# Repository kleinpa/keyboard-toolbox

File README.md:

# keyboard-toolkit

This repository contains tools for designing computer keyboards using
code. It brings together [KiCad](https://gitlab.com/kicad/code/kicad),
[exdxf](https://ezdxf.mozman.at/),
[Shapely](https://github.com/Toblerity/Shapely), and
[Bazel](https://bazel.build/) to hopefully make building keyboards a
little bit more like building a web site. Designing hardware with code
ideally enables fast iteration on key positions other design choices
with the support of an automated build system. It also means that a
single source of truth can be used to generate both the electrical
schematic and firmware.

## Overview

To build a keyboard with this library, just write a [small python
program](examples/build_numpad17.py) that generates a list of key
positions (and a few other things) and records that information in a
Keyboard protobuf message. Tools in this repository can use the
Keyboard message to generate PCBs, plates, firmware, and more. Some
post-processing, like PCB routing, will need to be done by hand but
hopefully it's less work than the alternatives.

Once a program exists to generate the keyboard definition, the Bazel
build system can be used to feed it's output into the generator tools
provided by this reposiory.

## Features

### Output Generation

- Generate Switch plates in DXF, SVG formats
- Generate unrouted PCBs with all required components
- [QMK info.json files](https://beta.docs.qmk.fm/developing-qmk/qmk-reference/reference_info_json)
- Generate [KLE JSON](http://www.keyboard-layout-editor.com/) data
- (Untested) Generate FR4 switch plates

### Input and Processing

- Load [KLE JSON](http://www.keyboard-layout-editor.com/) data
- Generate form-fitting PCBs and Plates based on the key arrangment
- Configure switch matrix positions based on the key arrangment

### Microcontrollers

- ATmega32u4
- Pro Micro
- (Untested) STM32F072

### Switchs

For now this project is focused on switch-specific PCBs.

- [Cherry MX](https://deskthority.net/wiki/Cherry_MX) compatible
- (WIP) [Kailh PG1350](https://deskthority.net/wiki/Kailh_PG1350_series)
- (WIP) [ALPS](https://deskthority.net/wiki/Alps_SKCL/SKCM_series) compatible

### Cases

Keyboard case come in many differnet styles are some of the least
trivial parts to generate. To keep things simple this repository only
supports the "PCB-to-Base-Plate Sandwich". This is a minimalist
approach where the PCB is attached to a base plate with standoffs and
an optional switch plate is 'floating' on the switches. Additional
case types may be added eventually and would be a welcome addition to
this library.

## Getting Started

This project uses the Bazel build system internally and also provides
build rules for downstream projects. Additionally, PCB file
processing is provided by the
[`kicad-bazel`](https://github.com/kleinpa/kicad-bazel) project which
works by building KiCAD from source
([issue](https://github.com/kleinpa/kicad-bazel/issues/2)). All tools
that interact with PCBs unfortunately depend on all of KiCAD's build
dependencies.

## Bazel Build Rules

It makes sense to use some tool to generate the keyboard proto and
here is an example of stock Baezl rules can be used to make that
happen:

```python
py_binary(
    name = "build_kbxyz",
    srcs = ["build_kbxyz.py"],
    deps = [
        "//kbtb:keyboard_lib",
    ],
)

genrule(
    name = "kbxyz_proto",
    outs = ["kbxyz.pb"],
    cmd = "$(execpath :build_kbxyz) $@",
    exec_tools = [":build_kbxyz"],
)
```

### build_keyboard

This is the main entry point to the output generation tools provided by this repository.

```python
load("@keyboard_toolbox//kbtb:defs.bzl", "build_keyboard")

build_keyboard(
    name = "kbxyz",
    src = ":kbxyz_proto",
)
```

The following files can be requested from this rule:

- `kbxyz.svg`
- `kbxyz.kicad_pcb`
- `kbxyz-info.json`
- `kbxyz_plate_top.dxf`
- `kbxyz_plate_top.kicad_pcb`
- `kbxyz_plate_bottom.dxf`
- `kbxyz_plate_bottom.kicad_pcb`

### kbpb_from_kle

This is an experimenal build rule that can produce a basic keyboard
from a kle file is also provided. It's probably more flexible to just
do this via python like in the genrule example above.

```python
load("@keyboard_toolbox//kbtb:defs.bzl", "kbpb_from_kle")

kbpb_from_kle(
    name = "kbxyz_proto",
    src = "kbxyz-kle.json",
)
```

## The Future

The biggest question that remains unanswered is: _Why just keyboards?_
If there's one thing I've figured out while working on this project is
that the idea of generating electronic hardware with software is worth
exploring more.

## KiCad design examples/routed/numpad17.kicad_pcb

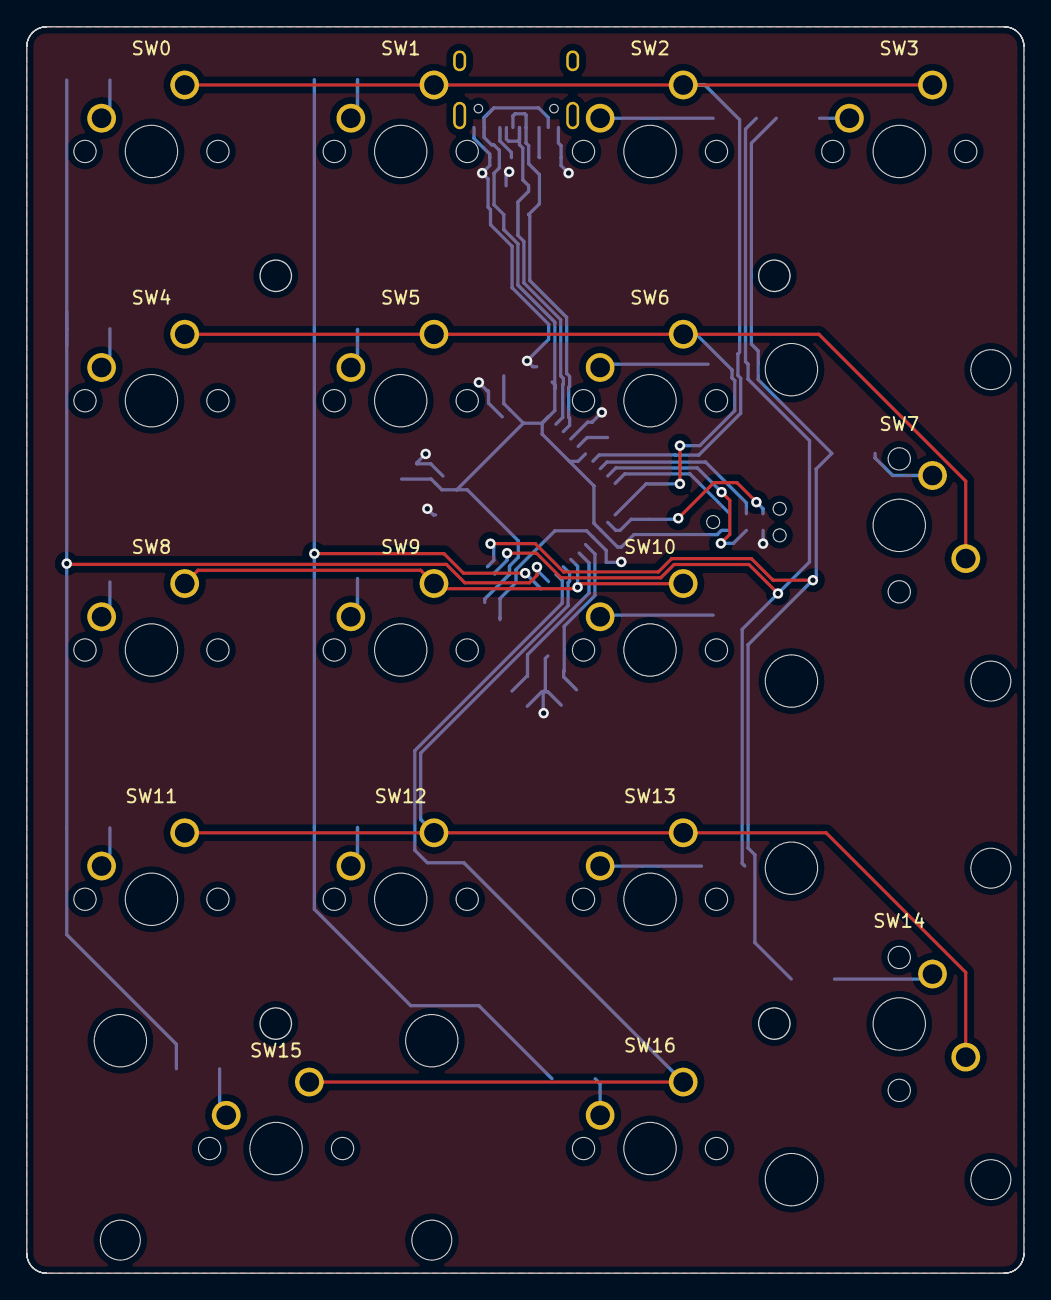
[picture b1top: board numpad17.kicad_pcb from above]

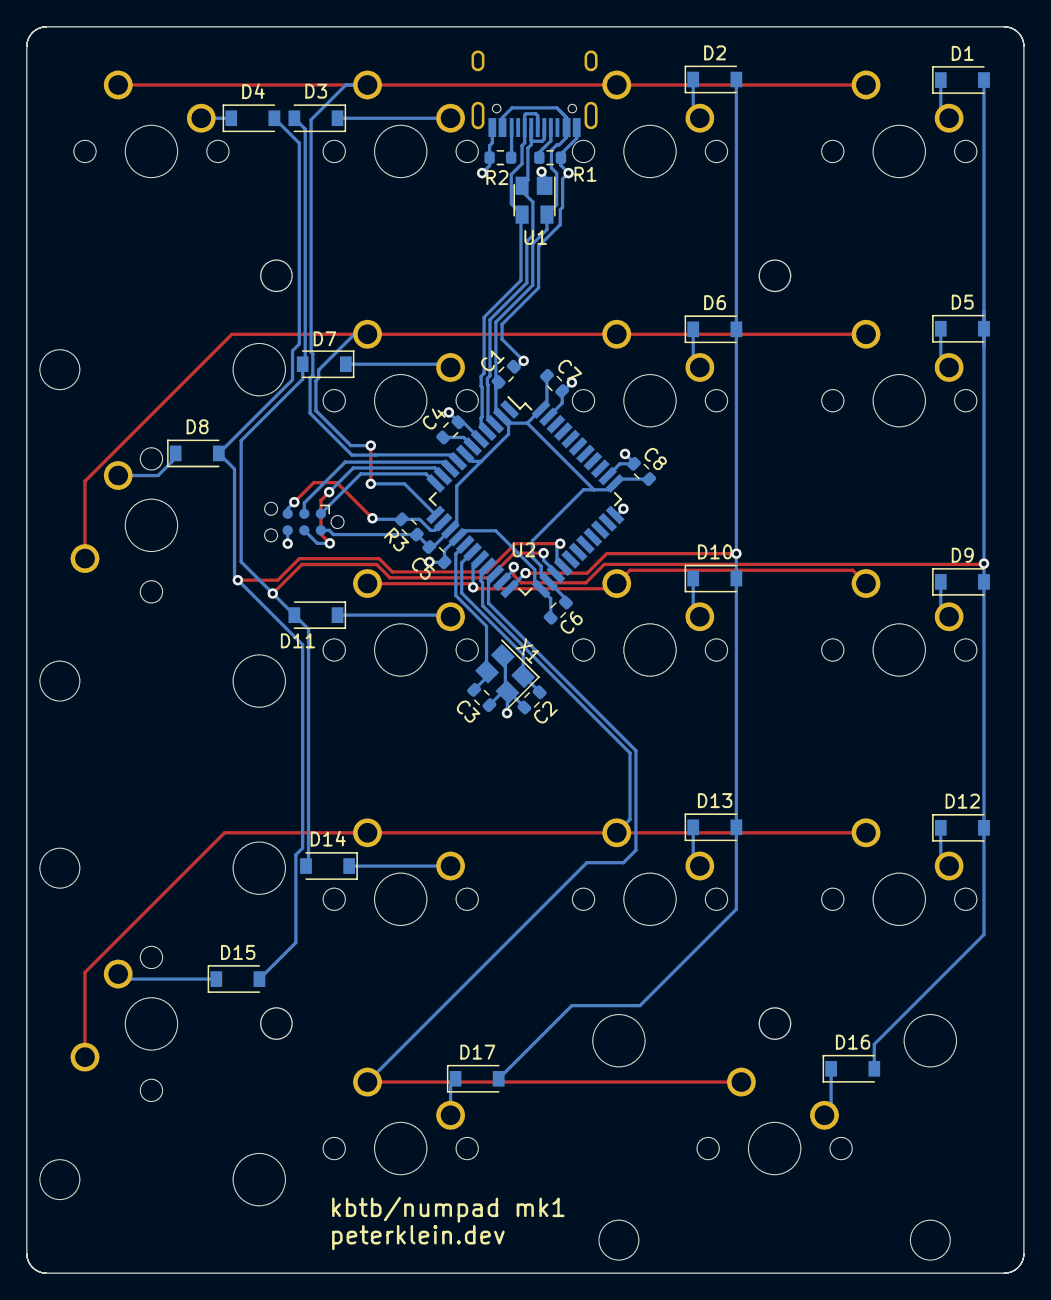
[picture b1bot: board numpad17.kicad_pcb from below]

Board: 2 copper layers, 76.2 x 95.2 mm, 53 parts (33 on the bottom side), 39 nets.

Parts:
C1: 10 µF; R_0603_1608Metric
C2, C3: 22 pF; R_0603_1608Metric
C4: 1 µF; R_0603_1608Metric
C5, C6, C7, C8: 0.1 µF; R_0603_1608Metric
D1, D2, D3, D4, D5, D6, D7, D8, D9, D10, D11, D12, D13, D14, D15, D16, D17: 4148; D_SOD-123
J1: HRO-TYPE-C-31-M-12
Jx1: Tag-Connect_TC2030-IDC-NL_2x03_P1.27mm_Vertical
R1, R2: 5.1 kΩ; R_0603_1608Metric
R3: 10 kΩ; R_0603_1608Metric
ST7, ST14, ST15: SW_Cherry_MX_2.00u_PCB; Stab_Cherry_MX_2.00u_PCB
SW0, SW1, SW2, SW3, SW4, SW5, SW6, SW7, SW8, SW9, SW10, SW11, SW12, SW13, SW14, SW15, SW16: SW_Cherry_MX_1.00u_PCB; SW_Cherry_MX_PCB
U1: SR05; SOT-143
U2: ATMEGA32U4-AU; TQFP-44_10x10mm_P0.8mm
X1: 16 MHz; Crystal_SMD_3225-4Pin_3.2x2.5mm

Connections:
GND: C1.1, C2.2, C3.2, C4.1, C5.1, C6.2, C7.1, C8.2, J1.1, J1.12, Jx1.6, R1.1, R2.2, U1.1, U2.5, U2.15, U2.23, U2.33, U2.35, U2.43, X1.2, X1.4
icsp-miso: Jx1.1, U2.11
icsp-mosi: Jx1.4, U2.10
icsp-reset: Jx1.5, R3.2, U2.13
icsp-sck: Jx1.3, U2.9
matrix-0: SW0.1, SW1.1, SW2.1, SW3.1, U2.8
matrix-1: SW4.1, SW5.1, SW6.1, SW7.1, U2.12
matrix-2: SW8.1, SW9.1, SW10.1, U2.18
matrix-3: SW11.1, SW12.1, SW13.1, SW14.1, U2.19
matrix-4: SW15.1, SW16.1, U2.20
matrix-5: D1.2, D5.2, D9.2, D12.2, D16.2, U2.21
matrix-6: D2.2, D6.2, D10.2, D13.2, D17.2, U2.22
matrix-7: D3.2, D7.2, D11.2, D14.2, U2.25
matrix-8: D4.2, D8.2, D15.2, U2.26
switch-diode-0: D1.1, SW0.2
switch-diode-1: D2.1, SW1.2
switch-diode-2: D3.1, SW2.2
switch-diode-3: D4.1, SW3.2
switch-diode-4: D5.1, SW4.2
switch-diode-5: D6.1, SW5.2
switch-diode-6: D7.1, SW6.2
switch-diode-7: D8.1, SW7.2
switch-diode-8: D9.1, SW8.2
switch-diode-9: D10.1, SW9.2
switch-diode-10: D11.1, SW10.2
switch-diode-11: D12.1, SW11.2
switch-diode-12: D13.1, SW12.2
switch-diode-13: D14.1, SW13.2
switch-diode-14: D15.1, SW14.2
switch-diode-15: D16.1, SW15.2
switch-diode-16: D17.1, SW16.2
ucap: C4.2, U2.6
usb-cc1: J1.4, R1.2
usb-cc2: J1.10, R2.1
usb-dn: J1.5, J1.7, U1.2, U2.3
usb-dp: J1.6, J1.8, U1.3, U2.4
usb-vcc: C1.2, C5.2, C6.1, C7.2, C8.1, J1.2, J1.11, Jx1.2, R3.1, U1.4, U2.2, U2.7, U2.14, U2.24, U2.34, U2.44
xtal1: C2.1, U2.17, X1.1
xtal2: C3.1, U2.16, X1.3

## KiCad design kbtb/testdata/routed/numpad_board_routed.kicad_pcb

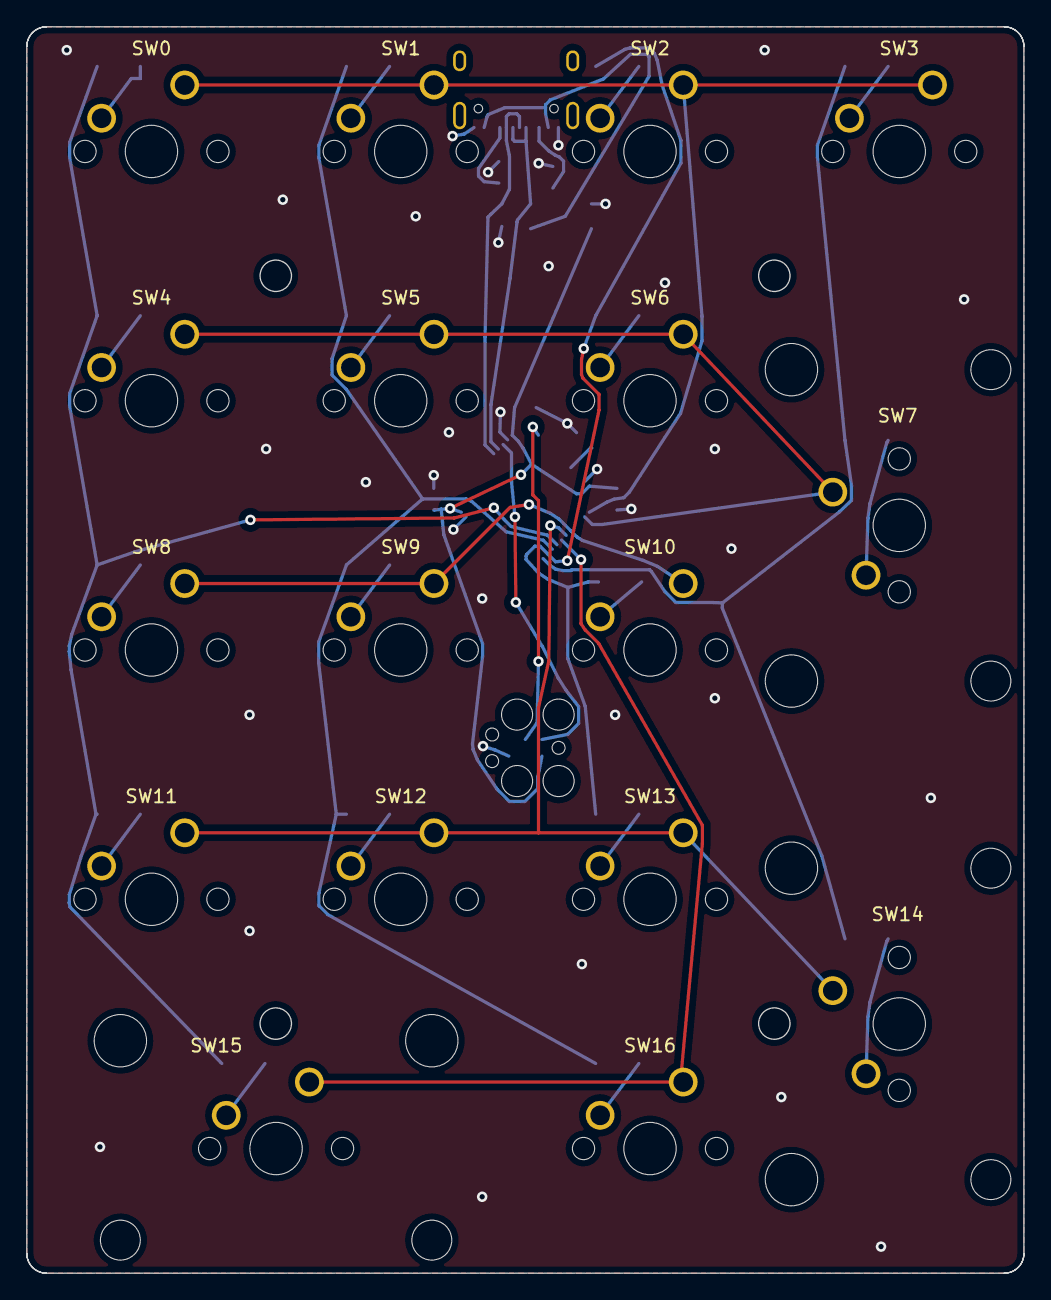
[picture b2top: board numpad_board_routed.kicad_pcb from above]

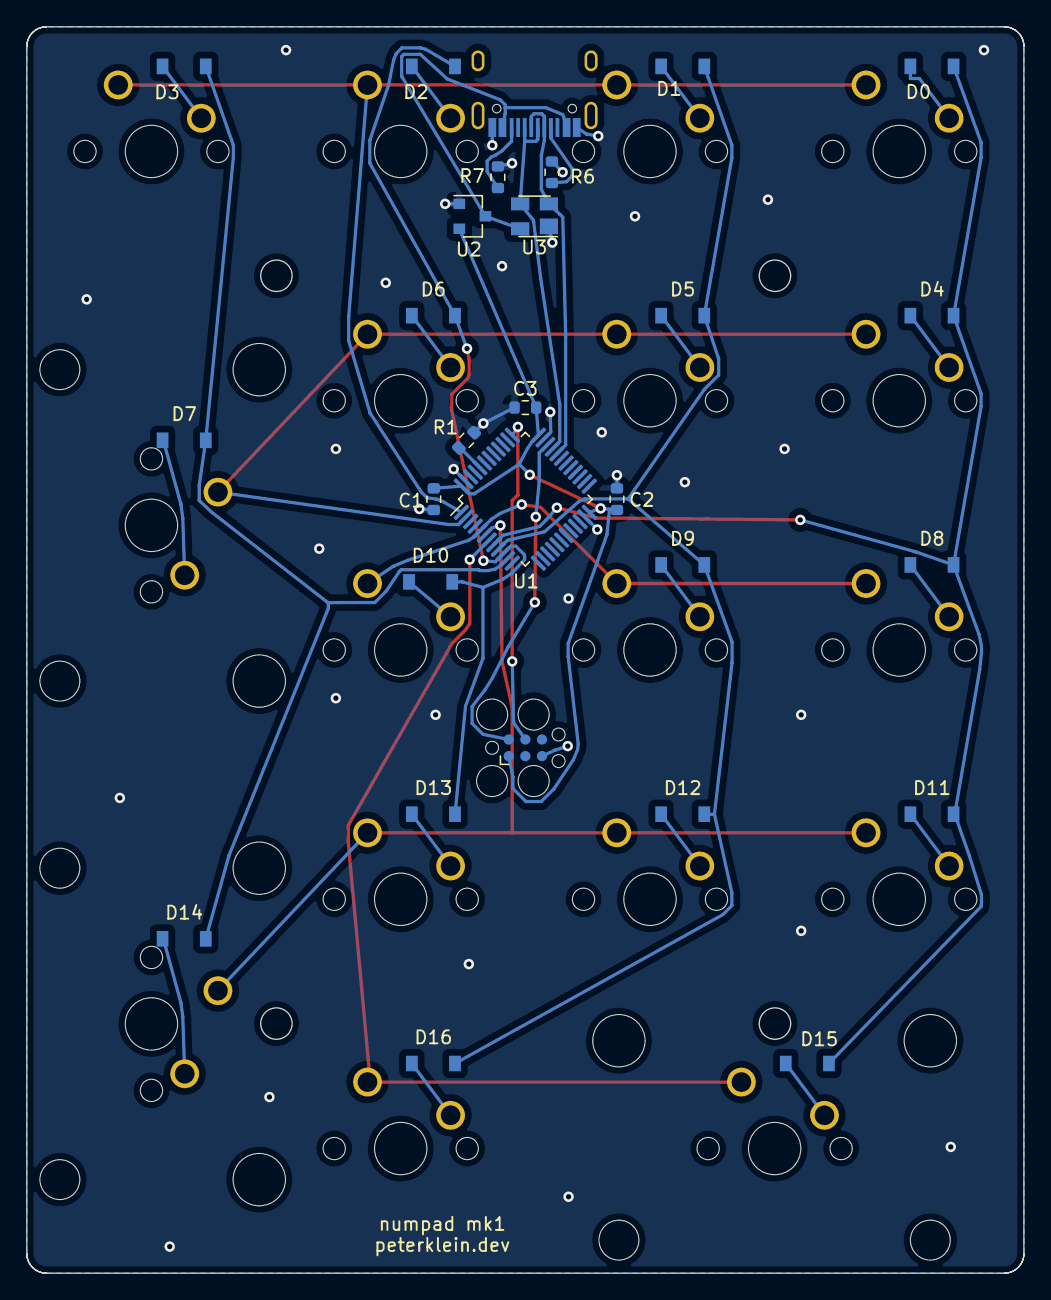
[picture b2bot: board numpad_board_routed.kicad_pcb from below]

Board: 2 copper layers, 76.2 x 95.2 mm, 48 parts (28 on the bottom side), 36 nets.

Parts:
C1, C2, C3: 0.1 µF; R_0603_1608Metric
D0, D1, D2, D3, D4, D5, D6, D7, D8, D9, D10, D11, D12, D13, D14, D15, D16: 4148; D_SOD-123
J1: HRO-TYPE-C-31-M-12
J2: Tag-Connect_TC2030-IDC-FP_2x03_P1.27mm_Vertical
R1: 10 kΩ; R_0603_1608Metric
R6, R7: 5.1 kΩ; R_0603_1608Metric
ST7, ST14, ST15: SW_Cherry_MX_2.00u_PCB; Stab_Cherry_MX_2.00u_PCB
SW0, SW1, SW2, SW3, SW4, SW5, SW6, SW7, SW8, SW9, SW10, SW11, SW12, SW13, SW14, SW15, SW16: SW_Cherry_MX_1.00u_PCB; SW_Cherry_MX_PCB
U1: STM32F072C8T6; LQFP-48_7x7mm_P0.5mm
U2: MCP1700T-3302E/TT; SOT-23
U3: SR05; SOT-143

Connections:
GND: C1.1, C2.2, C3.1, J1.1, J1.12, J2.5, R1.1, R6.2, R7.2, U1.23, U1.35, U1.47, U2.1, U3.1
boot: R1.2, U1.44
io-0: SW0.1, SW1.1, SW2.1, SW3.1, U1.1
io-1: SW4.1, SW5.1, SW6.1, SW7.1, U1.2
io-2: SW8.1, SW9.1, SW10.1, U1.5
io-3: SW11.1, SW12.1, SW13.1, SW14.1, U1.6
io-4: SW15.1, SW16.1, U1.7
io-5: D0.2, D4.2, D8.2, D11.2, D15.2, U1.8
io-6: D1.2, D5.2, D9.2, D12.2, D16.2, U1.9
io-7: D2.2, D6.2, D10.2, D13.2, U1.10
io-8: D3.2, D7.2, D14.2, U1.11
swdclk: J2.4, U1.37
swdio: J2.2, U1.34
switch-diode-0: D0.1, SW0.2
switch-diode-1: D1.1, SW1.2
switch-diode-2: D2.1, SW2.2
switch-diode-3: D3.1, SW3.2
switch-diode-4: D4.1, SW4.2
switch-diode-5: D5.1, SW5.2
switch-diode-6: D6.1, SW6.2
switch-diode-7: D7.1, SW7.2
switch-diode-8: D8.1, SW8.2
switch-diode-9: D9.1, SW9.2
switch-diode-10: D10.1, SW10.2
switch-diode-11: D11.1, SW11.2
switch-diode-12: D12.1, SW12.2
switch-diode-13: D13.1, SW13.2
switch-diode-14: D14.1, SW14.2
switch-diode-15: D15.1, SW15.2
switch-diode-16: D16.1, SW16.2
usb-cc1: J1.4, R6.1
usb-cc2: J1.10, R7.1
usb-dm: J1.5, J1.7, U1.32, U3.2
usb-dp: J1.6, J1.8, U1.33, U3.3
usb-vcc: J1.2, J1.11, U2.3, U3.4
vcc: C1.2, C2.1, C3.2, J2.1, U1.24, U1.36, U1.48, U2.2

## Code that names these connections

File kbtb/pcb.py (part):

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        pose=pose,
        value="ATMEGA32U4-AU",
        pins=[
            "pe6", "vcc", "dn", "dp", "ground", "ucap", "vcc", "pb0",
            "icsp_sck", "icsp_mosi", "icsp_miso", "pb7", "reset", "vcc",
            "ground", "xtal2", "xtal1", "pd0", "pd1", "pd2", "pd3", "pd5",
            "ground", "vcc", "pd4", "pd6", "pd7", "pb4", "pb5", "pb6", "pc6",
            "pc7", "ground", "vcc", "ground", "pf7", "pf6", "pf5", "pf4",
            "pf1", "pf0", "pin-42", "ground", "vcc"
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
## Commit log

2021-01-25 Add routing artifacts
2021-01-25 Clean up python
2021-01-25 Stub out matrix generator
2021-01-25 Add Key message to keyboard.proto
2021-01-25 Add make_qmk_header.py
2021-01-25 wip new boards
2021-01-26 Create a subfolder for each keyboard
2021-01-26 Remove mounting holes from plate by default
2021-01-26 Add test layout
2021-01-26 Commonize function to place keys in an arc
2021-01-26 Add make_plate.py to //toolbox:keyboard_lib deps
2021-01-26 Use common row function in layouts
2021-01-26 Remove switch silkscreen placement
2021-01-26 Add mk2 routed pcb
2021-01-30 Rework toolbox
2021-01-30 Switch to service
2021-01-30 Add basic support for non-1u keys
2021-02-09 Add support for keyboard-layout-editor.com compatible layouts
2021-02-09 Add documentation and improve structure
2021-02-09 Add convex hull outline type
2021-02-09 Add Bazel build rules for keyboard artifacts
2021-02-09 Add support for cherry stabilizers
2021-02-09 Uses obj.difference(...) instead of Polygon(...) to construct plate
2021-02-09 Downgrade protobuf to stable 3.14.0
2021-02-11 Reorganize into kbtb directory
2021-02-16 Store full outline polygon in keyboard proto
2021-03-08 Cleanup
2021-05-03 Add testdata examples and helper script
2021-05-03 Add slight plate cutout padding
2021-05-03 Add support for PCB-mount stabilizers and stm32
2021-05-03 Emit bom and centroid files with gerbers
2021-05-03 Add plate type selection and support bottom plates
2021-05-03 Fixup repo name and remove commented code
2021-05-09 Use bazelisk
2021-05-09 Separate controller and connector positioning
2021-05-09 Add testdata for creating gerbers from a routed PCB
2021-05-09 revert me
2021-05-15 Remove unused python dependencies
2021-05-15 Remove devcontainer
2021-05-15 Use kleinpa/kicad-bazel to manage KiCad dependencies
2021-05-15 Use bazelisk for VS Code tasks and build script
2021-05-15 Branding
2021-05-16 Remove unused fill_matrix funciton
2021-05-16 Add build rule for generating JLCPCB bom
2021-05-16 Overhaul PCB generation
2021-05-16 Simplify file handling
2021-05-17 Add support for Atmega32U4
2021-05-20 Add Stabilizers to keyboard.proto
2021-05-20 Update demonstration routed numpad PCB
2021-05-20 Add info text to PCB with fake hash
2021-05-20 Add build stamping
2021-05-21 Tweak default usb type c legacy layout
2021-05-21 Fix type error in cli.py
2021-05-23 Add build_keyboard rule and use external bom tool
2021-05-27 Update kicad-bazel to fix component rotation
2021-05-27 Rename examples
2021-05-27 Remove build stamping
2021-05-28 Tweak cap placement and use legless tag-connect
2021-05-28 Add numpad as ordered
2021-06-13 Name numpad17 consistently
2021-06-14 Generate QMK info.json instead of config.h
2021-06-21 Add experimental support for ATMega328P
2021-07-03 Fix stabilized switch cutout positioning
2021-07-04 Minor cleanup
2021-07-04 Move mounting screws to not interfere with stabilizers
2021-07-06 Use .json extension for qmk info files
2021-07-26 Use consistent controller pin ordering
2021-07-27 Add new switch types to keyboard.proto
2021-07-27 Clean up build_numpad17.py
2021-07-27 Generate QMK info.json config for STM32F072
2021-07-27 Use more compact TPD4E05U06 ESD chip
2021-07-27 Add documentation
2021-07-27 Remove unnecessary qmk_keyboard build rule
2021-07-27 Rework and simplify examples, remove kbpb_from_kle build rule
2021-07-27 Remove unnecessary file
2021-10-13 Add first-pass usb hub support
2022-11-18 Add build rule for kle json
2024-10-09 Use bzlmod
